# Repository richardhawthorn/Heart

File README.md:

### Description

LED Heart

<div id="link">
	<a href="http://www.deluxecapacitor.com/projects/view/16">Project Page</a>
</div>

### Features

- 20 LED display
- Charlieplex LED control
- Built in microphone and amplifier
- ATTINY44 processor
- 3V operation @ 1Mhz or 8Mhz
- 1x button
- ICSP port
- Holes for necklace chain

### License

This work is licensed under a Creative Commons Attribution-ShareAlike 4.0 International License.

<br />
Designed by <a xmlns:cc="http://creativecommons.org/ns#" href="http://www.richardhawthorn.com" property="cc:attributionName" rel="cc:attributionURL" target="_blank">Richard Hawthorn</a><br />
<a rel="license" href="http://creativecommons.org/licenses/by-sa/4.0/" target="_blank">View License</a>

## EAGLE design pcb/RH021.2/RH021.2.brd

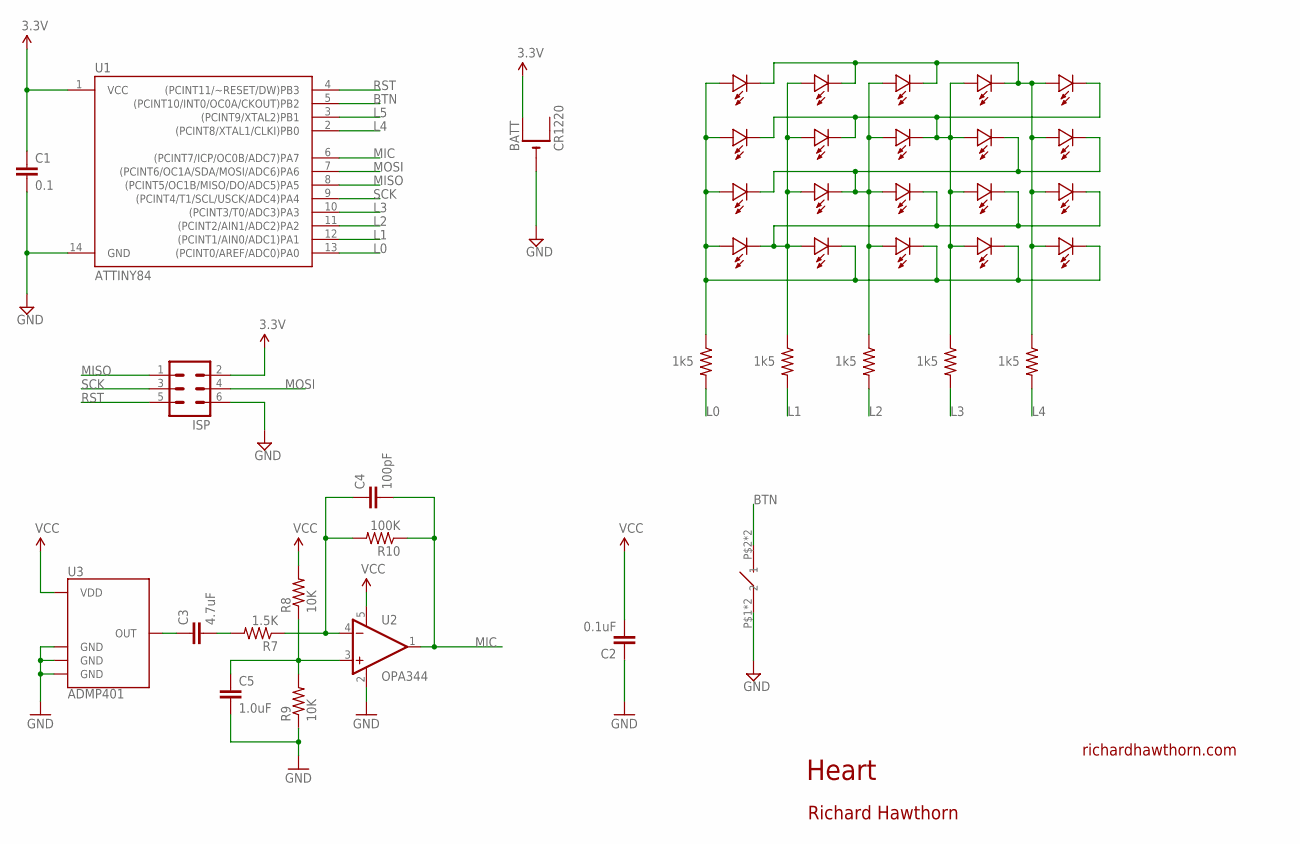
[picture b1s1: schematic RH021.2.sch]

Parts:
BATT: CR1220; CR1220-SMD
BTN1: TURTLE-3PIN
C1: 0.1; 0603-CAP
C2: 0.1uF; 0402-CAP
C3: 4.7uF; 0402-CAP
C4: 100pF; 0402-CAP
C5: 1.0uF; 0402-CAP
ISP: MA03-2
LED1, LED2, LED3, LED4, LED5, LED6, LED7, LED8, LED9, LED10, LED11, LED12, LED13, LED14, LED15, LED16, LED17, LED18, LED19, LED20: LED0603; 0603-LED
R1, R2, R3, R4, R5: 1k5; 0603-RES
R7: 1.5K; 0402-RES
R8, R9: 10K; 0402-RES
R10: 100K; 0402-RES
U1: ATTINY84; SO14
U2: OPA344; SOT23-5
U3: ADMP401

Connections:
BTN: BTN1.P$2 (2), BTN1.P$4 (2), U1.5 ((PCINT10/INT0/OC0A/CKOUT)PB2)
C7N$1: C3.1, U3.1 (OUT)
GND: BATT.-, BTN1.P$1 (1), BTN1.P$3 (1), C1.2, C2.1, C5.2, ISP.6, R9.1, U1.14 (GND), U2.2 (V-), U3.2 (GND), U3.4 (GND), U3.6 (GND)
L0: R1.2, U1.13 ((PCINT0/AREF/ADC0)PA0)
L1: R2.2, U1.12 ((PCINT1/AIN0/ADC1)PA1)
L2: R3.2, U1.11 ((PCINT2/AIN1/ADC2)PA2)
L3: R4.2, U1.10 ((PCINT3/T0/ADC3)PA3)
L4: R5.2, U1.2 ((PCINT8/XTAL1/CLKI)PB0)
L5: U1.3 ((PCINT9/XTAL2)PB1)
MIC: C4.2, R10.1, U1.6 ((PCINT7/ICP/OC0B/ADC7)PA7), U2.1 (OUT)
MISO: ISP.1, U1.8 ((PCINT5/OC1B/MISO/DO/ADC5)PA5)
MOSI: ISP.4, U1.7 ((PCINT6/OC1A/SDA/MOSI/ADC6)PA6)
unnamed: C4.1, R7.1, R10.2, U2.4 (-IN)
unnamed: C3.2, R7.2
unnamed: C5.1, R8.1, R9.2, U2.3 (+IN)
unnamed: LED2.PLUS, LED7.PLUS, LED12.PLUS, LED13.MINUS, LED14.MINUS, LED15.MINUS, LED16.MINUS, LED17.PLUS, R2.1
unnamed: LED1.PLUS, LED6.PLUS, LED11.PLUS, LED16.PLUS, LED17.MINUS, LED18.MINUS, LED19.MINUS, LED20.MINUS, R1.1
unnamed: LED1.MINUS, LED2.MINUS, LED3.MINUS, LED4.MINUS, LED5.PLUS, LED10.PLUS, LED15.PLUS, LED20.PLUS, R5.1
unnamed: LED4.PLUS, LED5.MINUS, LED6.MINUS, LED7.MINUS, LED8.MINUS, LED9.PLUS, LED14.PLUS, LED19.PLUS, R4.1
unnamed: LED3.PLUS, LED8.PLUS, LED9.MINUS, LED10.MINUS, LED11.MINUS, LED12.MINUS, LED13.PLUS, LED18.PLUS, R3.1
RST: ISP.5, U1.4 ((PCINT11/~RESET/DW)PB3)
SCK: ISP.3, U1.9 ((PCINT4/T1/SCL/USCK/ADC4)PA4)
VCC: BATT.+$1 (+), C1.1, C2.2, ISP.2, R8.2, U1.1 (VCC), U2.5 (V+), U3.5 (VDD)

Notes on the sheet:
Heart
richardhawthorn.com
Richard Hawthorn

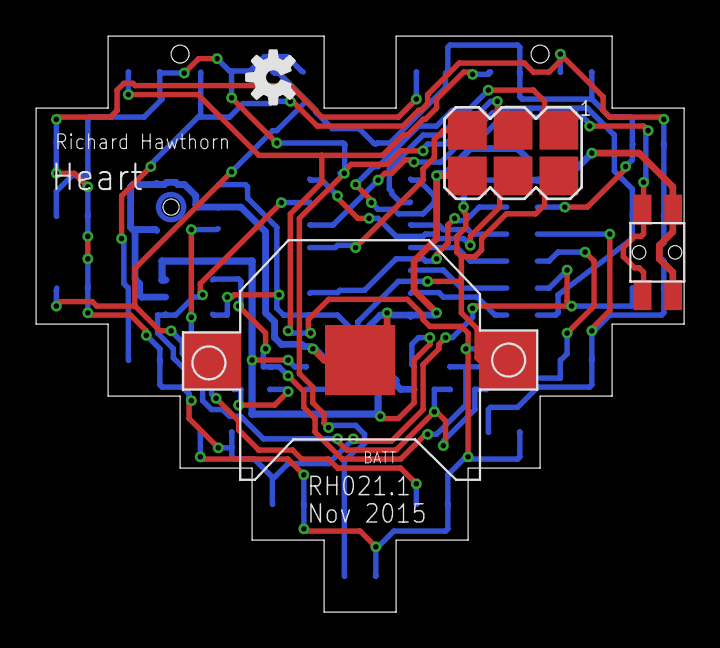
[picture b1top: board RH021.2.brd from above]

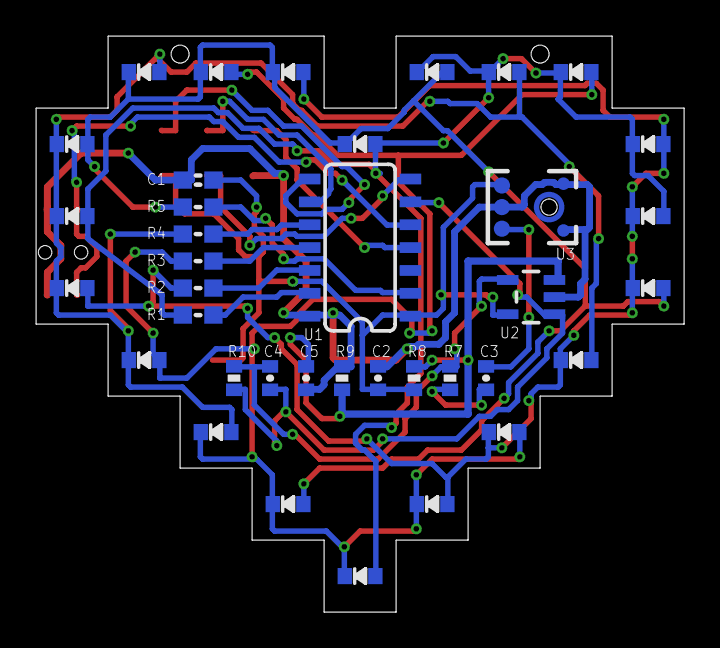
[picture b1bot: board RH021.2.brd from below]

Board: 2 copper layers, 36.0 x 32.0 mm, 41 parts (37 on the bottom side), 22 nets.

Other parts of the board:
U$3: OSHW-LOGO-S

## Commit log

2015-11-10 first version of the pcb
2015-11-10 updated labels
2015-11-10 added gerbers
2015-11-10 added images
2015-11-11 swap 2 leds
2015-12-01 Updated to more satisfying shape
2016-11-10 added readme

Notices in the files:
parts and their libraries:
SparkFun-Aesthetics: Licensing: CC v3.0 Share-Alike You are welcome to use this library for commercial purposes.
SparkFun-DigitalIC: Licensing: Creative Commons ShareAlike 4.0 International - https://creativecommons.org/licenses/by-sa/4.0
